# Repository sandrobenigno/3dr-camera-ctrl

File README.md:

3dr-camera-ctrl
===============

3DR Camera Control Board with USB Host

ArduCam PTP CHDK - Arduino based Remote CHDK Camera Control.
This firmware is part of the ArduCAM OSD Project: an open source Arduino based OSD and Camera Control.

For more information, documentation and usage instructions, please visit the project [Wiki](https://github.com/sandrobenigno/3dr-camera-ctrl/wiki)

<pre>
Author(s): Sandro Benigno
           Legacy PTP commands from Canon's PS-ReCSDK 1.1.0e
           Custom extended PTP commands from CHDK's PTP implementation
           USB host and PTP library from Oleg Mazurov - circuitsathome.com

Note: The PTP library used here was modified by the author.
      There are special characteristics needed to cover the scripting approach.
      The CHDK PTP Transaction has a wider RX buffer (reflected on the dataSize flag).
</pre>

This program is free software; you can redistribute it and/or
modify it under the terms of the GNU General Public License
as published by the Free Software Foundation; either version 2+
of the License, or (at your option) any later version.

This program is distributed in the hope that it will be useful,
but WITHOUT ANY WARRANTY; without even the implied warranty of
MERCHANTABILITY or FITNESS FOR A PARTICULAR PURPOSE.  See the
GNU General Public License for more details.

You should have received a copy of the GNU General Public License
along with this program. If not, see <http://www.gnu.org/licenses/>.

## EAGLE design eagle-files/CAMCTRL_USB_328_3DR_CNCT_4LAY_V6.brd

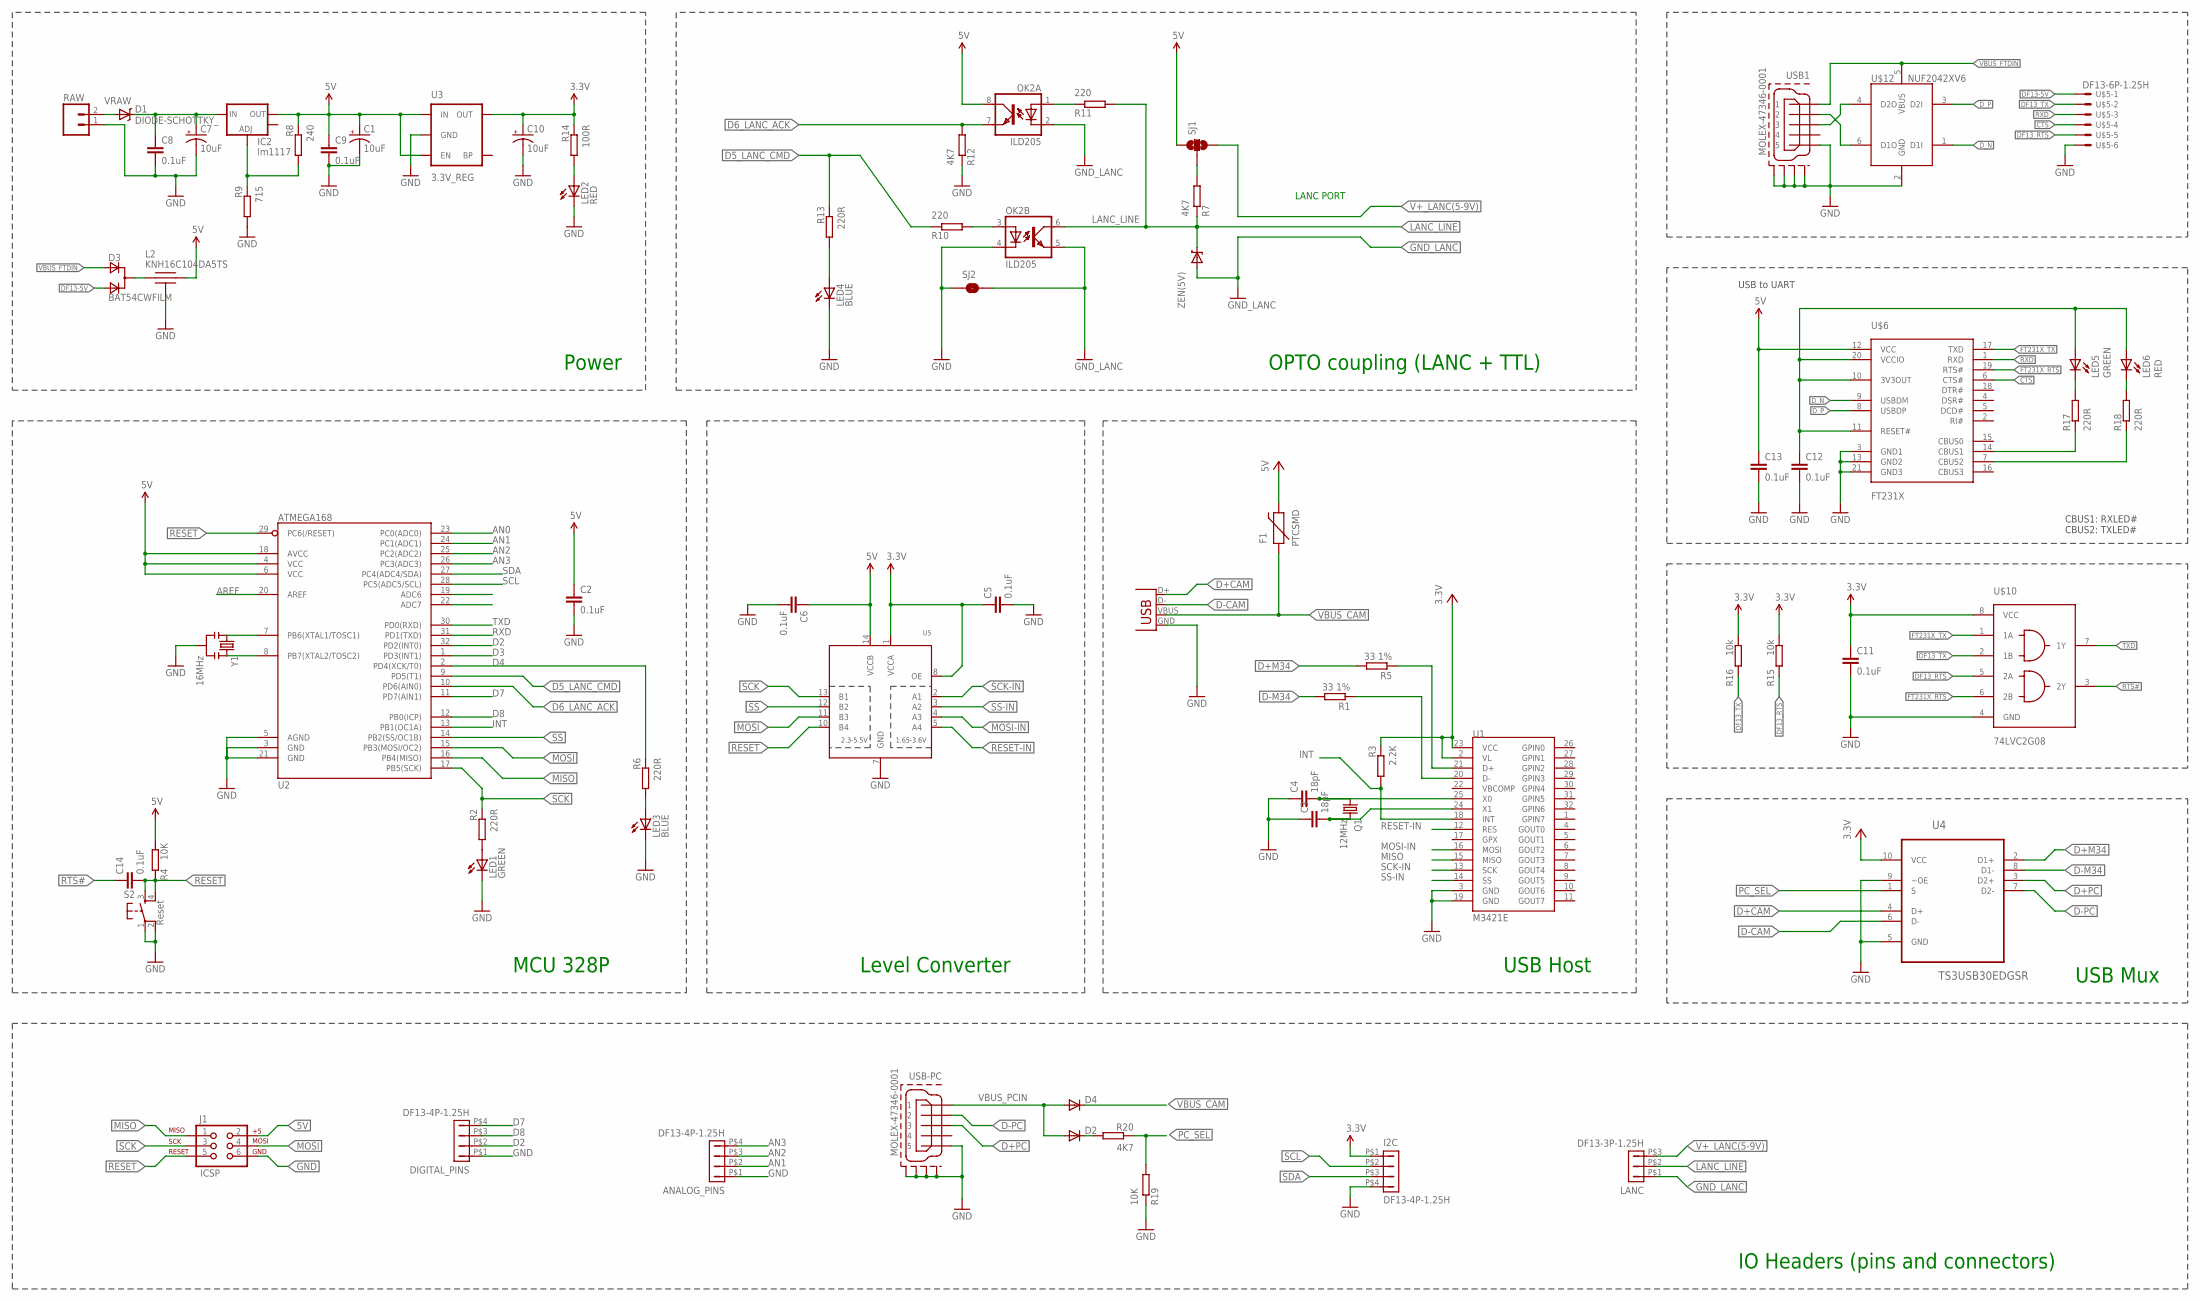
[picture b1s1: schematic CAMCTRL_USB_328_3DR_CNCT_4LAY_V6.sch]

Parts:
ANALOG_PINS: DF13-4P-1.25H; DF13A-4P-1.25H
C1, C7, C10: 10uF; EIA3216
C2, C5, C6, C8, C9, C11, C12, C13, C14: 0.1uF; 0402-CAP
C3, C4: 18pF; 0402-CAP
D1: DIODE-SCHOTTKY_; SMA-DIODE
D2, D4: DIODE-0603; 0603-DIO
D3: BAT54CWFILM; SOT323
DIGITAL_PINS: DF13-4P-1.25H; DF13A-4P-1.25H
F1: PTCSMD; PTC-1206
I2C: DF13-4P-1.25H; DF13A-4P-1.25H
IC2: lm1117; SOT223
J1: ICSP; 2X3
L2: KNH16C104DA5TS; KYOCERA-KNH16-DA
LANC: DF13-3P-1.25H; DF13A-3P-1.25H
LED1, LED5: GREEN; 0603-LED
LED2, LED6: RED; 0603-LED
LED3, LED4: BLUE; 0603-LED
OK2: ILD205; SOIC08
Q1: 12MHz; CRYSTAL-SMD-5X3
R1, R5: 33 1%; 0402-RES
R2, R6, R13, R17, R18: 220R; 0402-RES
R3: 2.2K; 0402-RES
R4, R19: 10K; 0402-RES
R7, R12, R20: 4K7; 0402-RES
R8: 240; 0402-RES
R9: 715; 0402-RES
R10, R11: 220; 0402-RES
R14: 100R; 0402-RES
R15, R16: 10k; 0402-RES
RAW: M02PTH; 1X02
S2: Reset; TACTILE_SWITCH_SMD
SJ1: SOLDERJUMPER_2WAYPASTE2&3; SJ_3_PASTE2&3
SJ2: SOLDERJUMPER-OLDNO; SJ_2S-NO
U1: M3421E; TQFP32-5MM
U2: ATMEGA168; TQFP32-08
U3: 3.3V_REG; SOT23-5
U4: TS3USB30EDGSR; SOP50P490X110-10N
U5: TXS0104PWR; TSSOP14
U$5: DF13-6P-1.25H; DF13A-6P-1.25H
U$6: FT231X; QFN20
U$10: 74LVC2G08; VFSOP-8
U$12: NUF2042XV6; SOT563-6
USB1: MOLEX-47346-0001
USB-PC: MOLEX-47346-0001
USB_HOST: USB-A-SMD; USB-A-S-NOSILK-FEMALE
Y1: 16MHz; RESONATOR-SMD
ZEN(5V): (5V); 0603-DIO

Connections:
3.3V: C5.P$1 (1), C10.A (+), C11.P$1 (1), I2C.P$1 (1), R3.P$1 (1), R14.P$1 (1), R15.P$1 (1), R16.P$1 (1), U1.2 (VL), U1.23 (VCC), U3.5 (OUT), U4.10 (VCC), U5.1 (VCCA), U5.8 (OE), U$10.8 (VCC)
5V: C1.A (+), C2.P$1 (1), C6.P$1 (1), C9.P$1 (1), C13.P$1 (1), F1.2, IC2.2 (OUT), J1.2, L2.P$2, OK2.8 (COL), R4.P$2 (2), R8.P$1 (1), SJ1.1, U2.4 (VCC), U2.6 (VCC), U2.18 (AVCC), U3.1 (IN), U3.3 (EN), U5.14 (VCCB), U$6.12 (VCC)
AN0: U2.23 (PC0(ADC0))
AN1: ANALOG_PINS.P$2 (2), U2.24 (PC1(ADC1))
AN2: ANALOG_PINS.P$3 (3), U2.25 (PC2(ADC2))
AN3: ANALOG_PINS.P$4 (4), U2.26 (PC3(ADC3))
AREF: U2.20 (AREF)
CTS: U$5.4, U$6.6 (CTS#)
D2: DIGITAL_PINS.P$2 (2), U2.32 (PD2(INT0))
D3: U2.1 (PD3(INT1))
D4: R6.P$1 (1), U2.2 (PD4(XCK/T0))
D5_LANC_CMD: R10.P$1 (1), R13.P$1 (1), U2.9 (PD5(T1))
D6_LANC_ACK: OK2.7 (EMIT), R12.P$2 (2), U2.10 (PD6(AIN0))
D7: DIGITAL_PINS.P$4 (4), U2.11 (PD7(AIN1))
D8: DIGITAL_PINS.P$3 (3), U2.12 (PB0(ICP))
D+CAM: U4.4 (D+), USB_HOST.D+
D+M34: R5.P$2 (2), U4.2 (D1+)
D+PC: U4.3 (D2+), USB-PC.D+ (3)
D-CAM: U4.6 (D-), USB_HOST.D-
D-M34: R1.P$2 (2), U4.8 (D1-)
D-PC: U4.7 (D2-), USB-PC.D- (2)
DF13-5V: D3.3 (A2), U$5.1
DF13_RTS: R15.P$2 (2), U$5.5, U$10.5 (2A)
DF13_TX: R16.P$2 (2), U$5.2, U$10.2 (1B)
D_N: U$6.9 (USBDM), U$12.1 (D1I)
D_P: U$6.8 (USBDP), U$12.3 (D2I)
FT231X_RTS: U$6.19 (RTS#), U$10.6 (2B)
FT231X_TX: U$6.17 (TXD), U$10.1 (1A)
GND: ANALOG_PINS.P$1 (1), C1.C (-), C2.P$2 (2), C3.P$1 (1), C4.P$1 (1), C5.P$2 (2), C6.P$2 (2), C7.C (-), C8.P$2 (2), C9.P$2 (2), C10.C (-), C11.P$2 (2), C12.P$2 (2), C13.P$2 (2), DIGITAL_PINS.P$1 (1), I2C.P$4 (4), J1.6, L2.P$3, L2.P$4, L2.P$5, LED1.C, LED2.C, LED3.C, LED4.C, OK2.4 (C), R9.P$2 (2), R12.P$1 (1), R19.P$1 (1), RAW.1, S2.1, S2.2, SJ2.1, U1.3 (GND), U1.19 (GND), U2.3 (GND), U2.5 (AGND), U2.21 (GND), U3.2 (GND), U4.5 (GND), U4.9 (~OE), U5.7 (GND), U$5.6, U$6.3 (GND1), U$6.13 (GND2), U$6.21 (GND3), U$10.4 (GND), U$12.2 (GND), USB1.GND (5), USB1.GND1, USB1.GND2, USB1.GND3, USB1.GND4, USB-PC.GND (5), USB-PC.GND1, USB-PC.GND2, USB-PC.GND3, USB-PC.GND4, USB_HOST.GND, Y1.2
GND_LANC: LANC.P$1 (1), OK2.2 (C), OK2.5 (EMIT), SJ2.2, ZEN(5V).A
INT: R3.P$2 (2), U1.18 (INT), U2.13 (PB1(OC1A))
LANC_LINE: LANC.P$2 (2), OK2.6 (COL), R7.P$1 (1), R11.P$2 (2), ZEN(5V).C
MISO: J1.1, U1.15 (MISO), U2.16 (PB4(MISO))
MOSI: J1.4, U2.15 (PB3(MOSI/OC2)), U5.11 (B3)
MOSI-IN: U1.16 (MOSI), U5.4 (A3)
unnamed: OK2.3 (A), R10.P$2 (2)
unnamed: U2.7 (PB6(XTAL1/TOSC1)), Y1.1
unnamed: U2.8 (PB7(XTAL2/TOSC2)), Y1.3
unnamed: LED1.A, R2.P$2 (2)
unnamed: C4.P$2 (2), Q1.1, U1.25 (X0)
unnamed: R5.P$1 (1), U1.21 (D+)
unnamed: R1.P$1 (1), U1.20 (D-)
unnamed: C3.P$2 (2), Q1.3 (2), U1.24 (X1)
unnamed: IC2.1 (ADJ), R8.P$2 (2), R9.P$1 (1)
unnamed: OK2.1 (A), R11.P$1 (1)
unnamed: LED3.A, R6.P$2 (2)
unnamed: R7.P$2 (2), SJ1.2
unnamed: D3.1 (C), L2.P$1
unnamed: LED4.A, R13.P$2 (2)
unnamed: U$12.6 (D1O), USB1.D- (2)
unnamed: U$12.4 (D2O), USB1.D+ (3)
unnamed: C12.P$1 (1), LED5.A, LED6.A, U$6.10 (3V3OUT), U$6.11 (RESET#), U$6.20 (VCCIO)
unnamed: R17.P$1 (1), U$6.14 (CBUS1)
unnamed: R18.P$1 (1), U$6.7 (CBUS2)
unnamed: LED5.C, R17.P$2 (2)
unnamed: LED2.A, R14.P$2 (2)
unnamed: LED6.C, R18.P$2 (2)
unnamed: D1.A, RAW.2
unnamed: D2.C, R20.P$2 (2)
PC_SEL: R19.P$2 (2), R20.P$1 (1), U4.1 (S)
RESET: C14.P$2 (2), J1.5, R4.P$1 (1), S2.3, S2.4, U2.29 (PC6(/RESET)), U5.10 (B4)
RESET-IN: U1.12 (RES), U5.5 (A4)
RTS#: C14.P$1 (1), U$10.3 (2Y)
RXD: U2.31 (PD1(TXD)), U$5.3, U$6.1 (RXD)
SCK: J1.3, R2.P$1 (1), U2.17 (PB5(SCK)), U5.13 (B1)
SCK-IN: U1.13 (SCK), U5.2 (A1)
SCL: I2C.P$2 (2), U2.28 (PC5(ADC5/SCL))
SDA: I2C.P$3 (3), U2.27 (PC4(ADC4/SDA))
SS: U2.14 (PB2(SS/OC1B)), U5.12 (B2)
SS-IN: U1.14 (SS), U5.3 (A2)
TXD: U2.30 (PD0(RXD)), U$10.7 (1Y)
V+_LANC(5-9V): LANC.P$3 (3), SJ1.3
VBUS_CAM: D4.C, F1.1, USB_HOST.VBUS
VBUS_FTDIN: D3.2 (A1), U$12.5 (VBUS), USB1.VBUS (1)
VBUS_PCIN: D2.A, D4.A, USB-PC.VBUS (1)
VRAW: C7.A (+), C8.P$1 (1), D1.C, IC2.3 (IN)

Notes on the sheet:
LANC PORT
OPTO coupling (LANC + TTL)
USB Host
Power
MCU 328P
Level Converter
IO Headers (pins and connectors)
USB to UART
CBUS1: RXLED# CBUS2: TXLED#
USB Mux

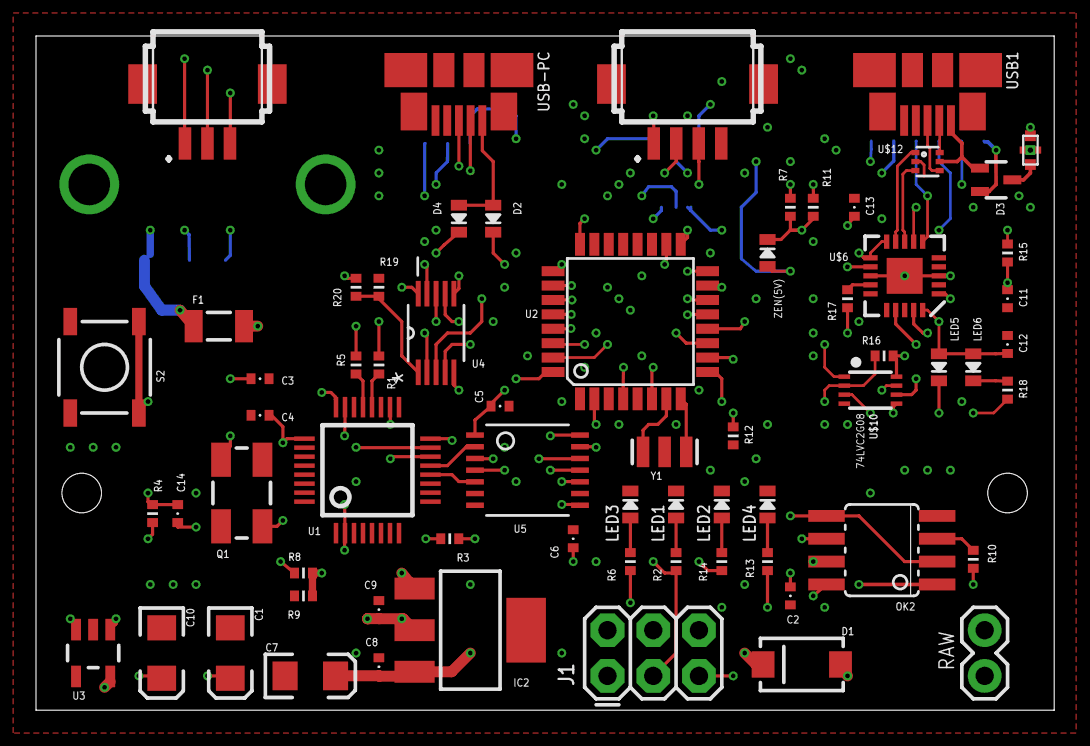
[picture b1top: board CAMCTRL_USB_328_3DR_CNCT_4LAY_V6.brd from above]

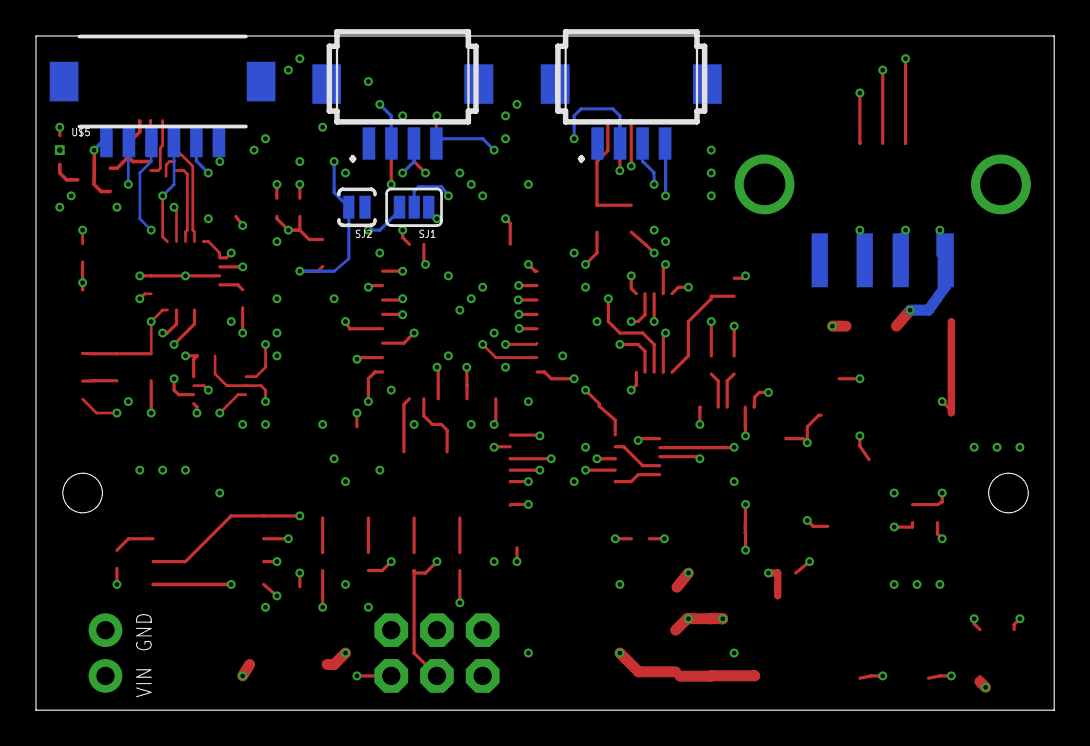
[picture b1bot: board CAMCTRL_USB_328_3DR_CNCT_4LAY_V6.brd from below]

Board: 4 copper layers, 56.6 x 37.5 mm, 72 parts (6 on the bottom side), 73 nets.

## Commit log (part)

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2014-01-24 Eagle CAD files
    Camera Control Board design, including schematic and the four- layer
    routing. It's under version 3 (prototyping fase).
2014-01-24 Cables and Wiring
    Description of cables and pin-headers. It's needed for interconnection
    and for having access to the broken out pins.
2014-01-24 Preliminar Code for Camera Control under CHDK PTP
    Code base for PTP camera control over USB Host.
    Note: This code is based on a test-bed hardware. It needs to be adapted
    to the final prototype. one
2014-02-12 Updated Code and Board
    Updated test code with new object info handling, zooming command and
    some extra clean-ups.
    Board updated with replaced LED's resistors.
2014-02-12 Correcting a small typo
    Wrong call to ptpobjhandleparser.h
2014-03-21 Prototype V2
    USB interruption line added;
    VCC vs 5V wrong propagation corrected.
2014-03-31 Prototype V2.1
    4k7 resistor added to the USB-Mux's "select" pin.
2014-04-01 Level Converter Replacement
    TXB0104PWR replaced by a TXS0104PWR (larger current draw on the IO). A
    10K OE resistor was added as well.
2014-05-09 APM 2.6 Triggering and MAVLink
    Triggering the board by Relay (Camera Control Inputs D3 or D8).
    Telemetry is grabed from APM 2.6 UART2
2014-05-09 PTP library improved for CHDK
    PTP library was changed to provide a wider RX Buffer over the USB
    packets (required by CHDK scripts execution with params)
2014-05-09 GeoShooting base-code for Camera Control over CHDK PTP
    Script called from a PTP transaction. It does receive telemetry data,
    takes a picture, creating or updating a file with GPS/IMU data. The
    filename is "geostore.csv". It is created in the folder session of taken
    pictures.
2014-06-09 Code for pure MAVLink Operation
    Biggest changes on Libraries and the base-code.
    Default operation uses MAVLink msgs for show lenses, foucus_lock,
    zooming and triggering.
    Default internal APM control:
    Shutter Setup --> RC8 (1000 - 2000)
    APM Input Channels:
2014-08-02 HardWare V6
    10K eliminated from the TXS0104PWR OE pin.
2014-08-02 Hardware V4 removed
    Removed "Hardware V4" from "eagle-files" folder.
2015-02-22 Update README.md
    Added GPL Version 3
2015-02-22 Added GPLv3
    Added GPL Version 3 all over the project files.
2015-03-20 GPLv2
    Moved from GPLv3 to GPLv2.
2015-03-23 GPLv2+
    Moved from GPLv2 to GPLv2+.
2015-03-23 GPLv2+
    CHDK script moved to GPLv2+.
2015-07-26 Initial commit. Converted files to Altium
    WARNING.... SCH and PCB not syncronised
    Not ready for production
2018-06-12 Wiki-images
    Images for the wiki pages.
2018-06-12 Images moved
    Images moved to a proper folder.
2021-02-15 Create LICENSE
2022-08-31 Adding the hw design in PDF
    The schematic of the 3DR Camera Control in PDF.

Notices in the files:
parts and their libraries:
SparkFun-DigitalIC: Licensing: CC v3.0 Share-Alike You are welcome to use this library for commercial purposes.
